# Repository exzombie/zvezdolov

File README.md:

# Zvezdolov

Zvezdolov ("Starcatcher") is a device for measuring stellar
brightness. I consists of a LED light mounted on a fishpole and
control knobs for adjusting the color and brightnes of the light. The
fishpole serves to keep the light as far away as practical from the
user, thus making it more similar to a point source. The user orients
the fishpole so that the light is visually near a star and adjusts the
color and brightness to match the star. A display on the control board
shows the apparent magnitude of the star.

This repository contains work in progress on a color version of such a
device. The previous prototype used a white LED and would not work
well on reddish stars. Currently, the circuit design is complete, but
untested. There is no software yet because the main LED driver chip is
not breadboard-friendly and a PCB has to be made first.

# Authors

Jure Varlec <jure.varlec@ad-vega.si>

Based on a white LED version by Andrej Lajovic
<andrej.lajovic@ad-vega.si>.

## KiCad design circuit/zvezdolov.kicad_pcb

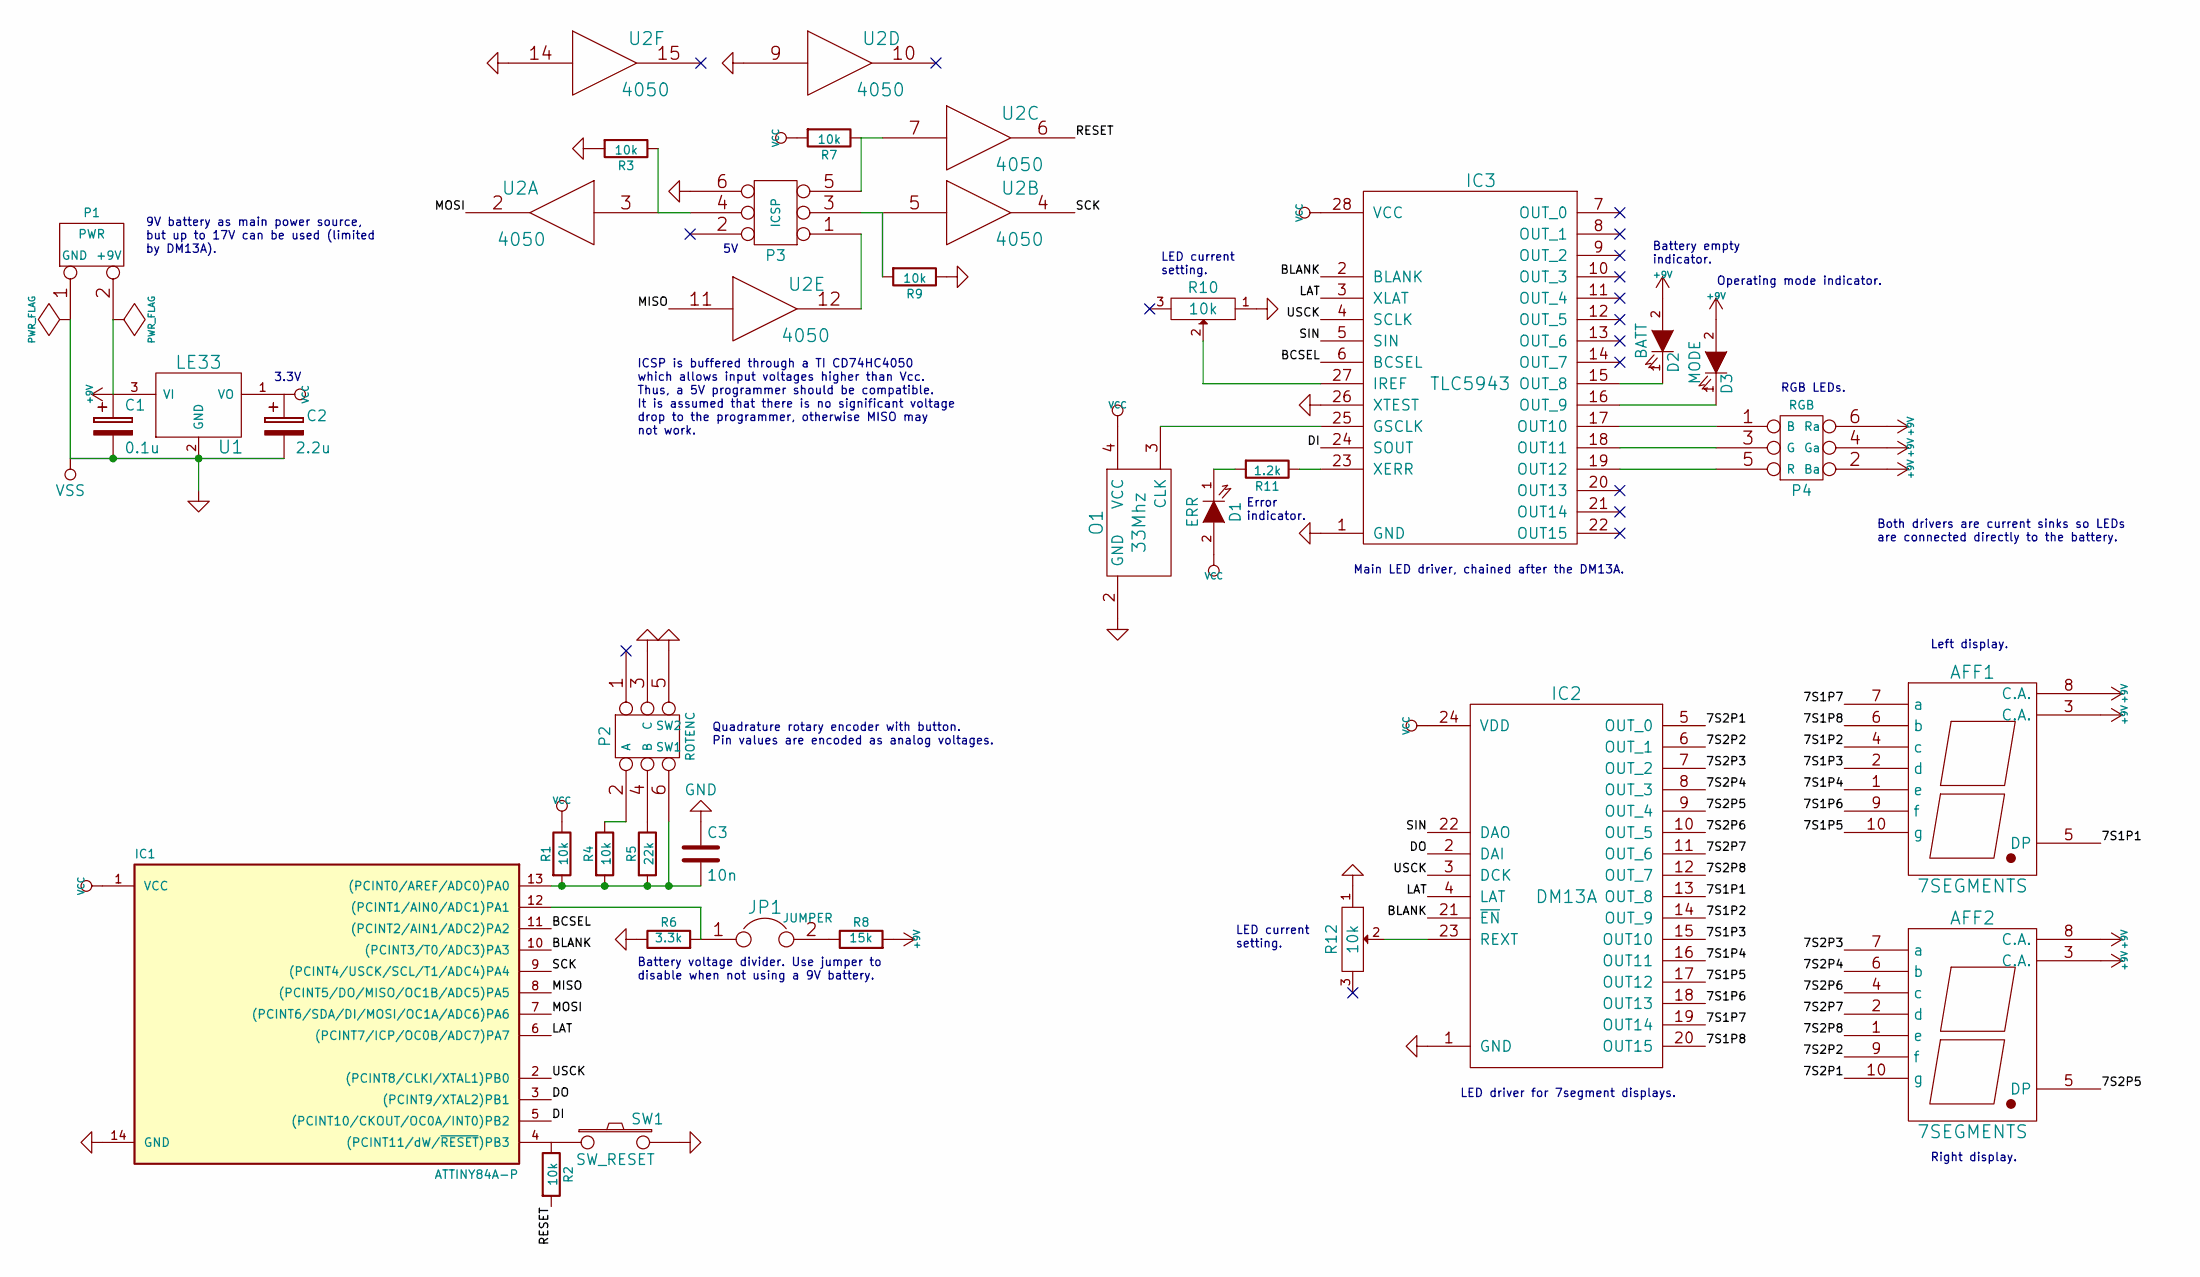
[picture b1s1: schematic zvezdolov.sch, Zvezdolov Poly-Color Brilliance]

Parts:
AFF1, AFF2: 7SEGMENTS; 7SegmentLED_LTS6760_LTS6780
C1: 0.1u; C_Rect_L7_W3.5_P5
C2: 2.2u; C_Radial_D5_L11_P2.5
C3: 10n; C_Rect_L7_W3.5_P5
D1: ERR; LED-5MM
D2: BATT; LED-5MM
D3: MODE; LED-5MM
IC1: ATTINY84A-P; DIP-14__300
IC2: DM13A; DIP-24__300
IC3: TLC5943; TSSOP-28_4.4x9.7mm_Pitch0.65mm
JP1: JUMPER; Pin_Header_Straight_1x02
O1: 33Mhz; Oscillator_SMD_7x5
P1: PWR; Pin_Header_Straight_1x02
P2: ROTENC; Pin_Header_Straight_2x03
P3: ICSP; Pin_Header_Straight_2x03
P4: RGB; Pin_Header_Straight_2x03
R1, R2, R3, R4, R7, R9: 10k; R3
R5: 22k; R3
R6: 3.3k; R3
R8: 15k; R3
R10, R12: 10k; TRIM
R11: 1.2k; R3
SW1: SW_RESET; SW_PUSH_SMALL
U1: LE33; TO-92_Molded_Wide_Reverse
U2: 4050; DIP-16__300

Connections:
+9V: AFF1.3 (C.A.), AFF1.8 (C.A.), AFF2.3 (C.A.), AFF2.8 (C.A.), C1.1, D2.2 (A), D3.2 (A), P1.2 (PM), P4.2, P4.4, P4.6, R8.2, U1.3 (VI)
/7S1P1: AFF1.5 (DP), IC2.13 (OUT_8)
/7S1P2: AFF1.4 (c), IC2.14 (OUT_9)
/7S1P3: AFF1.2 (d), IC2.15 (OUT10)
/7S1P4: AFF1.1 (e), IC2.16 (OUT11)
/7S1P5: AFF1.10 (g), IC2.17 (OUT12)
/7S1P6: AFF1.9 (f), IC2.18 (OUT13)
/7S1P7: AFF1.7 (a), IC2.19 (OUT14)
/7S1P8: AFF1.6 (b), IC2.20 (OUT15)
/7S2P1: AFF2.10 (g), IC2.5 (OUT_0)
/7S2P2: AFF2.9 (f), IC2.6 (OUT_1)
/7S2P3: AFF2.7 (a), IC2.7 (OUT_2)
/7S2P4: AFF2.6 (b), IC2.8 (OUT_3)
/7S2P5: AFF2.5 (DP), IC2.9 (OUT_4)
/7S2P6: AFF2.4 (c), IC2.10 (OUT_5)
/7S2P7: AFF2.2 (d), IC2.11 (OUT_6)
/7S2P8: AFF2.1 (e), IC2.12 (OUT_7)
/BCSEL: IC1.11 ((PCINT2/AIN1/ADC2)PA2), IC3.6 (BCSEL)
/BLANK: IC1.10 ((PCINT3/T0/ADC3)PA3), IC2.21 (~EN), IC3.2 (BLANK)
/DI: IC1.5 ((PCINT10/CKOUT/OC0A/INT0)PB2), IC3.24 (SOUT)
/DO: IC1.3 ((PCINT9/XTAL2)PB1), IC2.2 (DAI)
/LAT: IC1.6 ((PCINT7/ICP/OC0B/ADC7)PA7), IC2.4 (LAT), IC3.3 (XLAT)
/MISO: IC1.8 ((PCINT5/DO/MISO/OC1B/ADC5)PA5), U2.11
/MOSI: IC1.7 ((PCINT6/SDA/DI/MOSI/OC1A/ADC6)PA6), U2.2
/RESET: R2.2, U2.6
/SCK: IC1.9 ((PCINT4/USCK/SCL/T1/ADC4)PA4), U2.4
/SIN: IC2.22 (DAO), IC3.5 (SIN)
/USCK: IC1.2 ((PCINT8/CLKI/XTAL1)PB0), IC2.3 (DCK), IC3.4 (SCLK)
unnamed: C3.2, IC1.13 ((PCINT0/AREF/ADC0)PA0), P2.6, R1.2, R4.2, R5.2
unnamed: D1.1 (K), R11.2
unnamed: D2.1 (K), IC3.15 (OUT_8)
unnamed: D3.1 (K), IC3.16 (OUT_9)
unnamed: IC1.4 ((PCINT11/dW/~RESET~)PB3), R2.1, SW1.1
unnamed: IC1.12 ((PCINT1/AIN0/ADC1)PA1), JP1.1, R6.2
unnamed: IC2.23 (REXT), R12.2
unnamed: IC3.17 (OUT10), P4.1
unnamed: IC3.18 (OUT11), P4.3
unnamed: IC3.19 (OUT12), P4.5
unnamed: IC3.23 (XERR), R11.1
unnamed: IC3.25 (GSCLK), O1.3 (CLK)
unnamed: IC3.27 (IREF), R10.2
unnamed: JP1.2, R8.1
unnamed: P2.2, R4.1
unnamed: P2.4, R5.1
unnamed: P3.1, U2.12
unnamed: P3.3, R9.2, U2.5
unnamed: P3.4, R3.1, U2.3
unnamed: P3.5, R7.1, U2.7
VCC: C2.1, D1.2 (A), IC1.1 (VCC), IC2.24 (VDD), IC3.28 (VCC), O1.4 (VCC), R1.1, R7.2, U1.1 (VO), U2.1 (VCC)
VSS: C1.2, C2.2, C3.1, IC1.14 (GND), IC2.1 (GND), IC3.1 (GND), IC3.26 (XTEST), O1.2 (GND), P1.1, P2.3, P2.5, P3.6, R3.2, R6.1, R9.1, R10.1, R12.1, SW1.2, U1.2 (GND), U2.8 (VSS), U2.9, U2.14

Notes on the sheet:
3.3V
Battery voltage divider. Use jumper to disable when not using a 9V battery.
9V battery as main power source, but up to 17V can be used (limited by DM13A).
Quadrature rotary encoder with button. Pin values are encoded as analog voltages.
LED driver for 7segment displays.
Battery empty indicator.
Main LED driver, chained after the DM13A.
Both drivers are current sinks so LEDs are connected directly to the battery.
Error indicator.
LED current setting.
Operating mode indicator.
RGB LEDs.
Left display.
Right display.
ICSP is buffered through a TI CD74HC4050 which allows input voltages higher than Vcc. Thus, a 5V programmer should be compatible. It is assumed that there is no significant voltage drop to the programmer, otherwise MISO may not work.

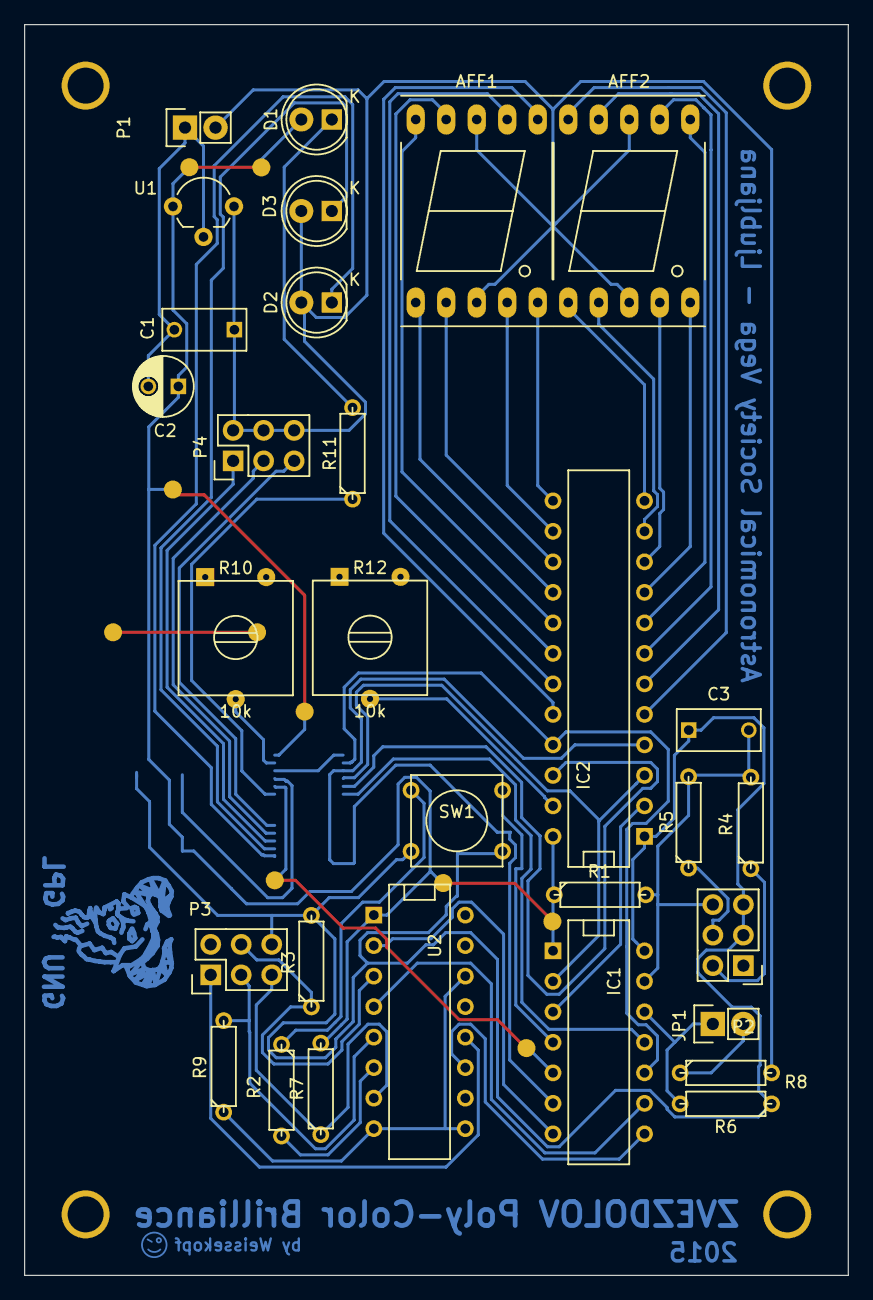
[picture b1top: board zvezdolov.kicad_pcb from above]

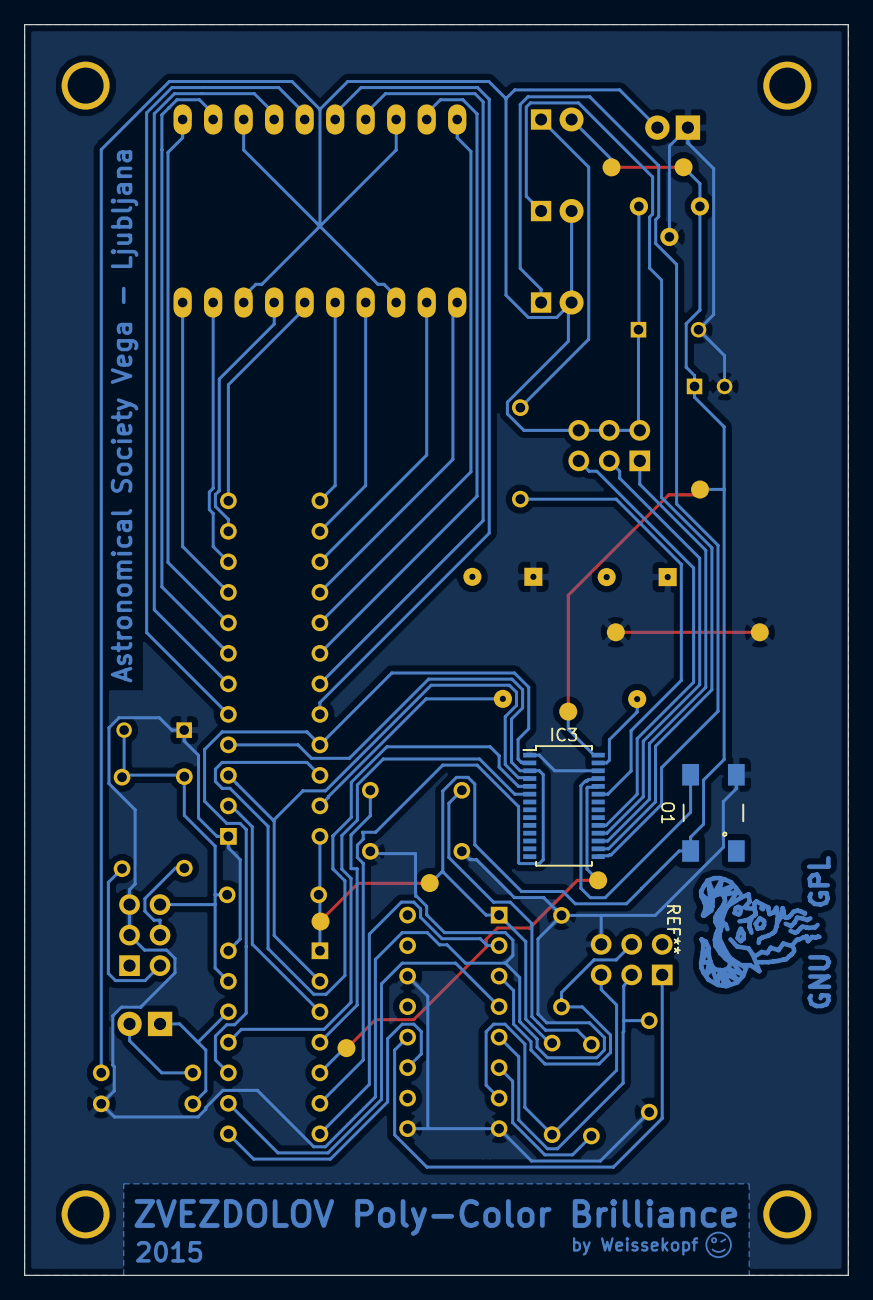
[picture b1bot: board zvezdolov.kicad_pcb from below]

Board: 2 copper layers, 68.6 x 104.1 mm, 36 parts (2 on the bottom side), 50 nets.

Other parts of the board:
MOUNT1, MOUNT2, MOUNT3, MOUNT4: MountingHole_3mm

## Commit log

2015-06-21 Initial import.
2015-06-21 Add a debounce capacitor to the encoder.
2015-06-21 Move some components slightly.
2015-06-21 PCB text tweaks.
2015-06-21 Add README, license and gitignore.
2015-06-26 Make the PCB considerably smaller.
2015-06-27 Fix texts, add logos and bump PCB revision.
2015-06-28 Extend gitignore.
2015-07-31 Move a wire pad from under IC3 where it was in the way.
2015-08-16 Fix the broken ICSP setup.
